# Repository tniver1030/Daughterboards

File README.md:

# Daughterboards
Various daughterboards and breakout not worth creating their own repo for

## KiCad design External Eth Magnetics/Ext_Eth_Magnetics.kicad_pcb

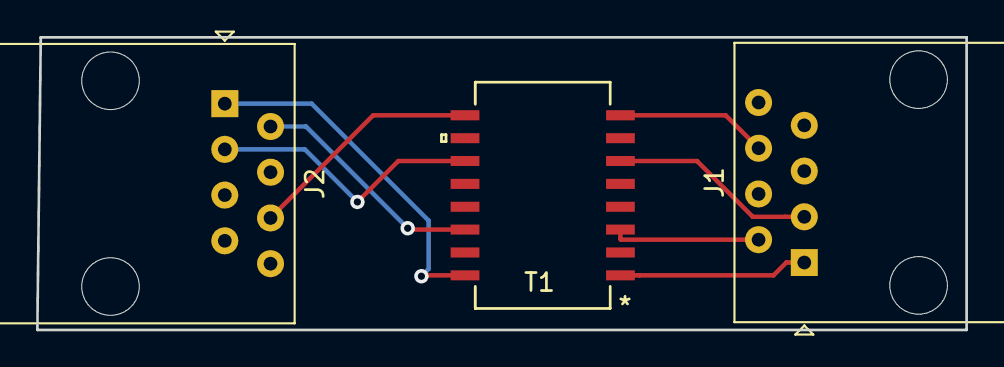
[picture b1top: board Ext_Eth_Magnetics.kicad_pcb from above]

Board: 2 copper layers, 51.6 x 16.3 mm, 3 parts (0 on the bottom side), 8 nets.

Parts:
J1, J2: RJ45; RJ45_Amphenol_54602-x08_Horizontal
T1: S558-5500-25-F

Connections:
unnamed: J1.1, T1.1
unnamed: J1.2, T1.3
unnamed: J1.3, T1.6
unnamed: J1.6, T1.8
unnamed: J2.1, T1.16
unnamed: J2.2, T1.14
unnamed: J2.3, T1.11
unnamed: J2.6, T1.9

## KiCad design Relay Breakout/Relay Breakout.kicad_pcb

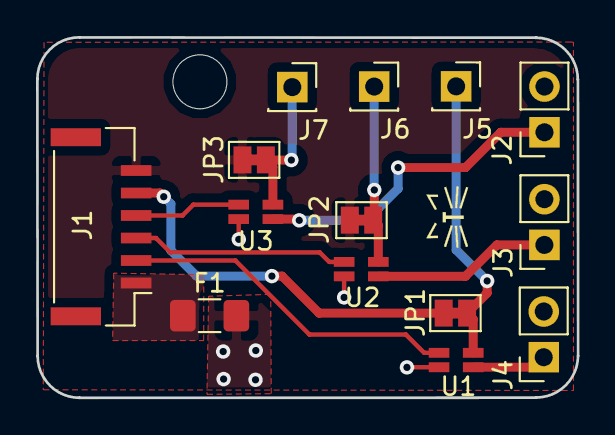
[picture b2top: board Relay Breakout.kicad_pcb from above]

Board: 2 copper layers, 30.0 x 20.0 mm, 14 parts (0 on the bottom side), 13 nets.

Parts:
F1: Fuse; Fuse_1206_3216Metric_Pad1.42x1.75mm_HandSolder
J1: Conn_01x06_Male; JST_GH_BM06B-GHS-TBT_1x06-1MP_P1.25mm_Vertical
J2, J3, J4: Conn_01x02_Female; PinSocket_1x02_P2.54mm_Vertical
J5, J6, J7: Conn_01x01_Female; PinSocket_1x01_P2.54mm_Vertical
JP1, JP2, JP3: SolderJumper_2_Bridged; SolderJumper-2_P1.3mm_Bridged_Pad1.0x1.5mm
U1, U2, U3: TLP3403R

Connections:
3V3DC: J1.5, JP1.2
5VDC: J1.6, JP2.2, JP3.2
GND: F1.2, J2.2, J3.2, J4.2, U1.2, U2.2, U3.2
GPIO1: J1.4, U3.1
GPIO2: J1.3, U2.1
GPIO3: J1.2, U1.1
unnamed: F1.1, J1.1
unnamed: J2.1, U3.3
unnamed: J3.1, U2.3
unnamed: J4.1, U1.3
unnamed: J5.1, JP1.1, U1.4
unnamed: J6.1, JP2.1, U2.4
unnamed: J7.1, JP3.1, U3.4

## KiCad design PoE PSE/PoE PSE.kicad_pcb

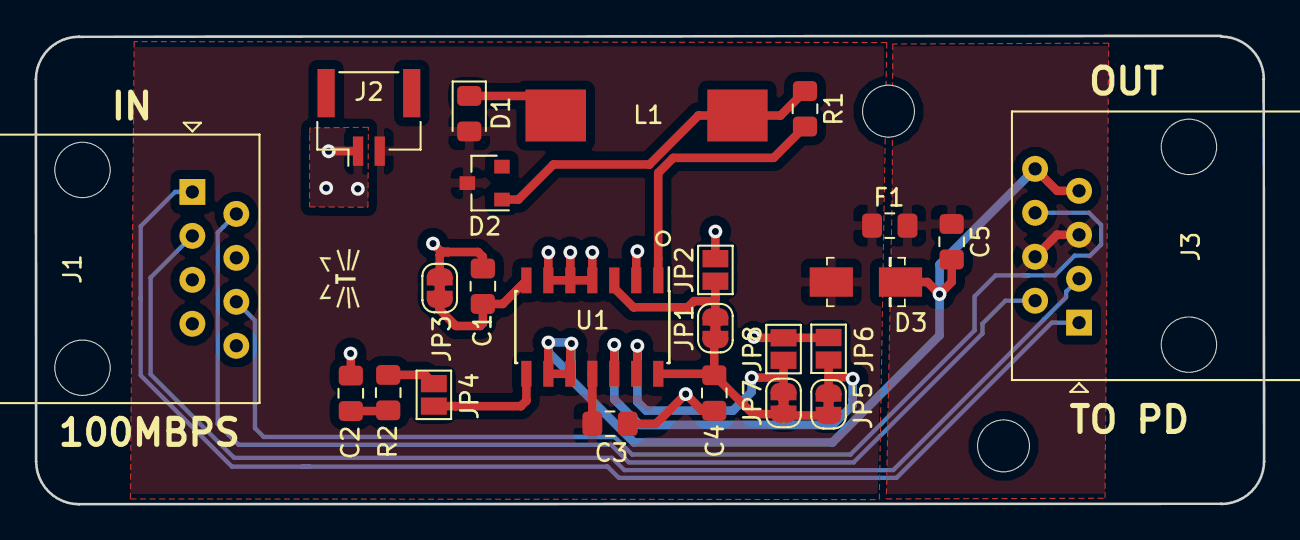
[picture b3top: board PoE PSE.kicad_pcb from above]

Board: 2 copper layers, 71.0 x 27.1 mm, 24 parts (0 on the bottom side), 19 nets.

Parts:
C1, C2, C4, C5: 0.1uF; C_0805_2012Metric_Pad1.15x1.40mm_HandSolder
C3: C; C_0805_2012Metric_Pad1.15x1.40mm_HandSolder
D1: LED; LED_0805_2012Metric_Pad1.15x1.40mm_HandSolder
D2: D; SOT-23
D3: D_TVS; DO-214AC
F1: Fuse; Fuse_0805_2012Metric_Pad1.15x1.40mm_HandSolder
J1, J3: RJ45; RJ45_Amphenol_54602-x08_Horizontal
J2: Conn_01x02; JST_GH_BM02B-GHS-TBT_1x02-1MP_P1.25mm_Vertical
JP1, JP3, JP5, JP7: SolderJumper_2_Bridged; SolderJumper-2_P1.3mm_Bridged_RoundedPad1.0x1.5mm
JP2, JP4, JP6, JP8: SolderJumper_2_Open; SolderJumper-2_P1.3mm_Open_Pad1.0x1.5mm
L1: INDUCTOR; SDR1005-103KL
R1, R2: R; R_0805_2012Metric_Pad1.15x1.40mm_HandSolder
U1: LTC4263; SOIC-14_3.9x8.7mm_P1.27mm

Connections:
ETH1: J1.1, J3.1
ETH2: J1.2, J3.2
ETH3: J1.3, J3.3
ETH6: J1.6, J3.6
unnamed: C1.1, JP3.1, U1.7
unnamed: C2.1, R2.2
unnamed: C5.1, F1.1, J3.4, J3.5
unnamed: C5.2, D3.1, J3.7, J3.8, U1.9, U1.10
unnamed: D1.1, L1.1
unnamed: D2.2, L1.2, R1.1
unnamed: JP1.2, JP2.1, U1.3
unnamed: JP4.1, U1.8
unnamed: JP4.2, R2.1
unnamed: JP5.2, JP6.1, U1.12
unnamed: JP7.2, JP8.1, U1.13
unnamed: R1.2, U1.1
VDD5: C4.1, JP1.1, JP5.1, JP7.1, U1.14
VDD48: C3.1, D1.2, D2.1, D3.2, F1.2, J2.2, U1.11
VSS: C1.2, C2.2, C3.2, C4.2, J2.1, JP2.2, JP3.2, JP6.2, JP8.2, U1.2, U1.4, U1.5, U1.6

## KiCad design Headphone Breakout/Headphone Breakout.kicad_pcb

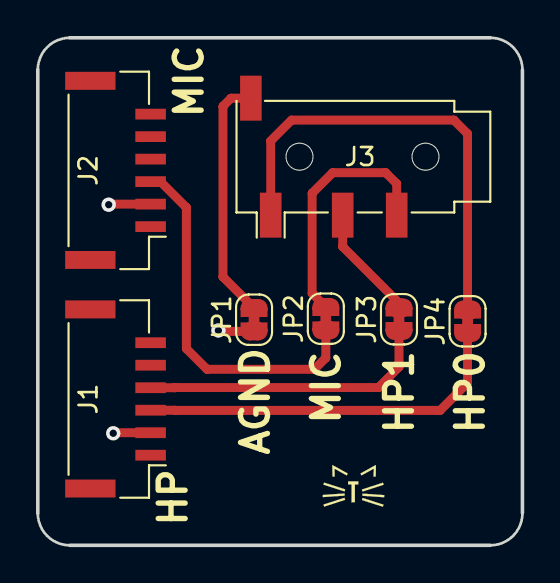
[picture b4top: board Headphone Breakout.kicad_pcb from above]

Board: 2 copper layers, 26.9 x 28.2 mm, 7 parts (0 on the bottom side), 11 nets.

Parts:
J1, J2: Conn_01x06_Male; JST_GH_BM06B-GHS-TBT_1x06-1MP_P1.25mm_Vertical
J3: AudioJack4_Ground; Jack_3.5mm_PJ320D_Horizontal
JP1, JP2, JP3, JP4: SolderJumper_2_Bridged; SolderJumper-2_P1.3mm_Bridged_RoundedPad1.0x1.5mm

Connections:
3V3: J1.5, J2.5
5V: J1.6, J2.6
AGND: J1.2, J2.2, JP1.1
DGND: J1.1, J2.1
HP0: J1.3, JP4.1
HP1: J1.4, JP3.1
MIC_0: J2.3, JP2.1
unnamed: J3.1, JP4.2
unnamed: J3.2, JP3.2
unnamed: J3.3, JP2.2
unnamed: J3.4, JP1.2

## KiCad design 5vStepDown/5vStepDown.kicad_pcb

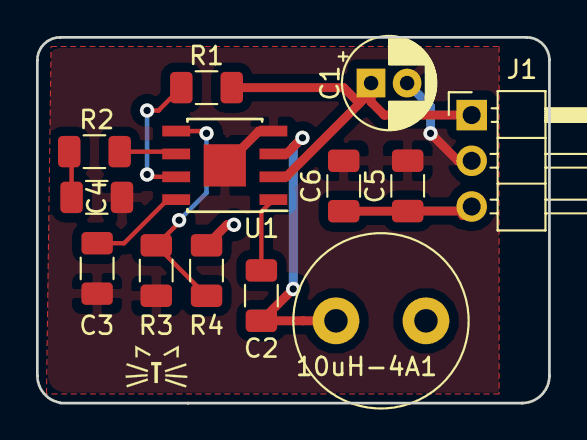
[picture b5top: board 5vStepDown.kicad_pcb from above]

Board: 2 copper layers, 28.4 x 20.3 mm, 13 parts (0 on the bottom side), 10 nets.

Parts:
10uH-4A1: INDUCTOR; L_Radial_D9.5mm_P5.00mm_Fastron_07HVP
C1: 10uF; CP_Radial_D5.0mm_P2.00mm
C2: 10nF; C_1206_3216Metric
C3: .1uF; C_1206_3216Metric
C4: 3.9nF; C_1206_3216Metric
C5, C6: 22uF; C_1206_3216Metric
J1: Conn_01x03_Male; PinHeader_1x03_P2.54mm_Horizontal
R1: R100K; R_1206_3216Metric
R2: 6.8k; R_1206_3216Metric
R3: 10k; R_1206_3216Metric
R4: 44.2k; R_1206_3216Metric
U1: MP2307; SOIC-8-1EP_3.9x4.9mm_P1.27mm_EP2.35x2.35mm

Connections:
GND: C1.2, C3.2, C5.2, C6.2, J1.2, R2.2, R3.2, U1.4, U1.9
INPUT: C1.1, J1.1, R1.2, U1.2
unnamed: 10uH-4A1.2, C2.2, U1.3
unnamed: C2.1, U1.1
unnamed: C3.1, U1.8
unnamed: C4.1, U1.6
unnamed: C4.2, R2.1
unnamed: R1.1, U1.7
unnamed: R3.1, R4.2, U1.5
OUTPUT: 10uH-4A1.1, C5.1, C6.1, J1.3, R4.1

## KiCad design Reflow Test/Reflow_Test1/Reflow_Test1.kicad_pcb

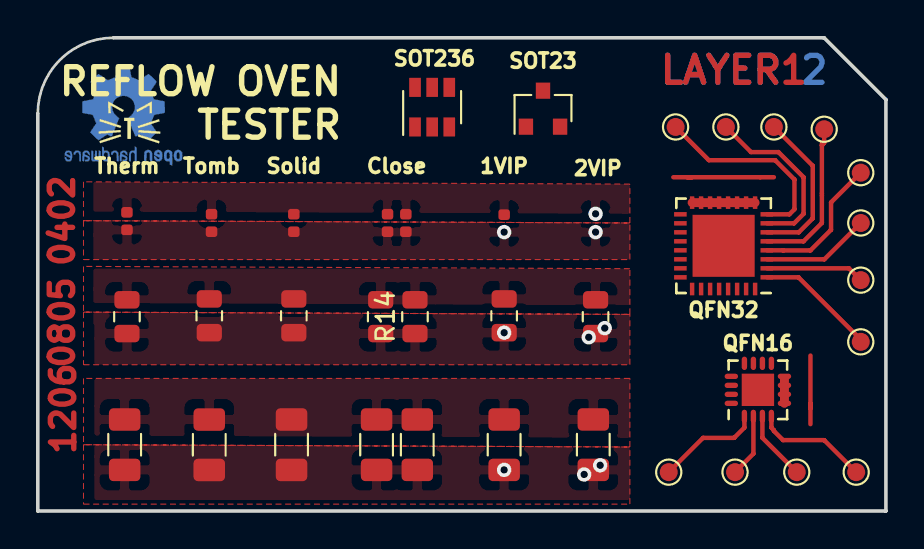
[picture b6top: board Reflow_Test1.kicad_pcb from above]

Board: 2 copper layers, 47.1 x 26.3 mm, 37 parts (0 on the bottom side), 16 nets.

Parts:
Q1: Q_NPN_BCE; SOT-23
R1, R4, R7, R10, R13, R16, R19: R; R_0402_1005Metric
R2, R5, R8, R11, R14, R17, R20: R; R_0805_2012Metric
R3, R6, R9, R12, R15, R18, R21: R; R_1206_3216Metric
TP1, TP2, TP3, TP4, TP5, TP6, TP7, TP8, TP9, TP10, TP11, TP12: TestPoint; TestPoint_Pad_D1.0mm
U1: PIC16F505-IMG; QFN-16-1EP_3x3mm_P0.5mm_EP1.8x1.8mm
U2: ATSAML21E15B-MUT; QFN-32-1EP_5x5mm_P0.5mm_EP3.45x3.45mm
U3: PAM8301; SOT-23-6

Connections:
GND: R1.2, R2.2, R3.2, R4.2, R5.2, R6.2, R7.2, R8.2, R9.2, R10.2, R11.2, R12.2, R13.2, R14.2, R15.2, R16.2, R17.2, R18.2, R19.2, R20.2, R21.2
unnamed: TP1.1, U2.4
unnamed: TP2.1, U2.5
unnamed: TP3.1, U2.3
unnamed: TP4.1, U1.4
unnamed: TP5.1, U2.6
unnamed: TP6.1, U2.2
unnamed: TP7.1, U2.7
unnamed: TP8.1, U2.1
unnamed: TP9.1, U2.8
unnamed: TP10.1, U1.1
unnamed: TP11.1, U1.2
unnamed: TP12.1, U1.3
unnamed: U1.5, U1.6, U1.7, U1.8
unnamed: U2.9, U2.10, U2.11, U2.12, U2.13, U2.14, U2.15, U2.16, U2.28
VCC: R1.1, R2.1, R3.1, R4.1, R5.1, R6.1, R7.1, R8.1, R9.1, R10.1, R11.1, R12.1, R13.1, R14.1, R15.1, R16.1, R17.1, R18.1, R19.1, R20.1, R21.1

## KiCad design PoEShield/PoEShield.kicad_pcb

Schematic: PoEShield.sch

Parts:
C1, C5: 0.1uF; C_0805_2012Metric_Pad1.15x1.40mm_HandSolder
C2: 22uF; C_1206_3216Metric_Pad1.42x1.75mm_HandSolder
C3: 1uF; C_1206_3216Metric_Pad1.42x1.75mm_HandSolder
C4: 10uF; C_1206_3216Metric_Pad1.42x1.75mm_HandSolder
C6, C7: 1nF 2kv; C_1206_3216Metric_Pad1.42x1.75mm_HandSolder
D1: SMAJ58JA; SMAJ58A-13-F
D2, D3: ABS2; Diode_Bridge_Diotec_ABS
F1: Fuse; Fuse_0805_2012Metric_Pad1.15x1.40mm_HandSolder
J1: RJ45; RJ45_Amphenol_54602-x08_Horizontal
J2: Conn_01x02_Male; JST_GH_BM02B-GHS-TBT_1x02-1MP_P1.25mm_Vertical
J3: Conn_01x03_Male; PinHeader_1x03_P2.54mm_Horizontal
L1: LQM2MPN4R7MG0L; L_0805_2012Metric_Pad1.15x1.40mm_HandSolder
R1: 287K; R_0805_2012Metric_Pad1.15x1.40mm_HandSolder
R2: 255; R_0805_2012Metric_Pad1.15x1.40mm_HandSolder
R3: 23.2k; R_0805_2012Metric_Pad1.15x1.40mm_HandSolder
R4: 1.62k; R_0805_2012Metric_Pad1.15x1.40mm_HandSolder
R5: 0; R_0805_2012Metric_Pad1.15x1.40mm_HandSolder
T1: S558-5500-25-F
U1: TPS2376-H; TI_SO-PowerPAD-8
U2: mEZS84801A
U3: PDQE10-Q48-S3-D; CONV_PDQE10-Q48-S3-D

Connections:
/3V3DC: J3.1, U2.17, U2.18
/12VDC: J3.3, U2.13, U2.14
/-VREG: C4.2, C7.2, U2.15, U2.16, U2.19, U2.20, U3.5
/VDD: C1.1, C2.1, D1.1, D2.1, D3.1, F1.2, J2.2, R3.1, U1.8
/VREG: C4.1, C6.2, J3.2, U3.3
/VSS: C1.2, D1.2, D2.2, D3.2, R1.2, R2.2, R4.2, U1.4, U1.9
unnamed: C2.2, C3.2, C5.2, C7.1, J2.1, U1.5, U3.1
unnamed: C3.1, C5.1, C6.1, L1.2, U3.2
unnamed: D2.3, T1.7
unnamed: D2.4, T1.2
unnamed: D3.3, J1.7, J1.8
unnamed: D3.4, J1.4, J1.5
unnamed: F1.1, L1.1
unnamed: J1.1, T1.1
unnamed: J1.2, T1.3
unnamed: J1.3, T1.6
unnamed: J1.6, T1.8
unnamed: R1.1, U1.1
unnamed: R2.1, U1.2
unnamed: R3.2, R4.1, U1.7
unnamed: R5.1, U1.6
unnamed: R5.2, U3.6
unnamed: T1.9, U2.10
unnamed: T1.11, U2.7
unnamed: T1.14, U2.6
unnamed: T1.16, U2.5

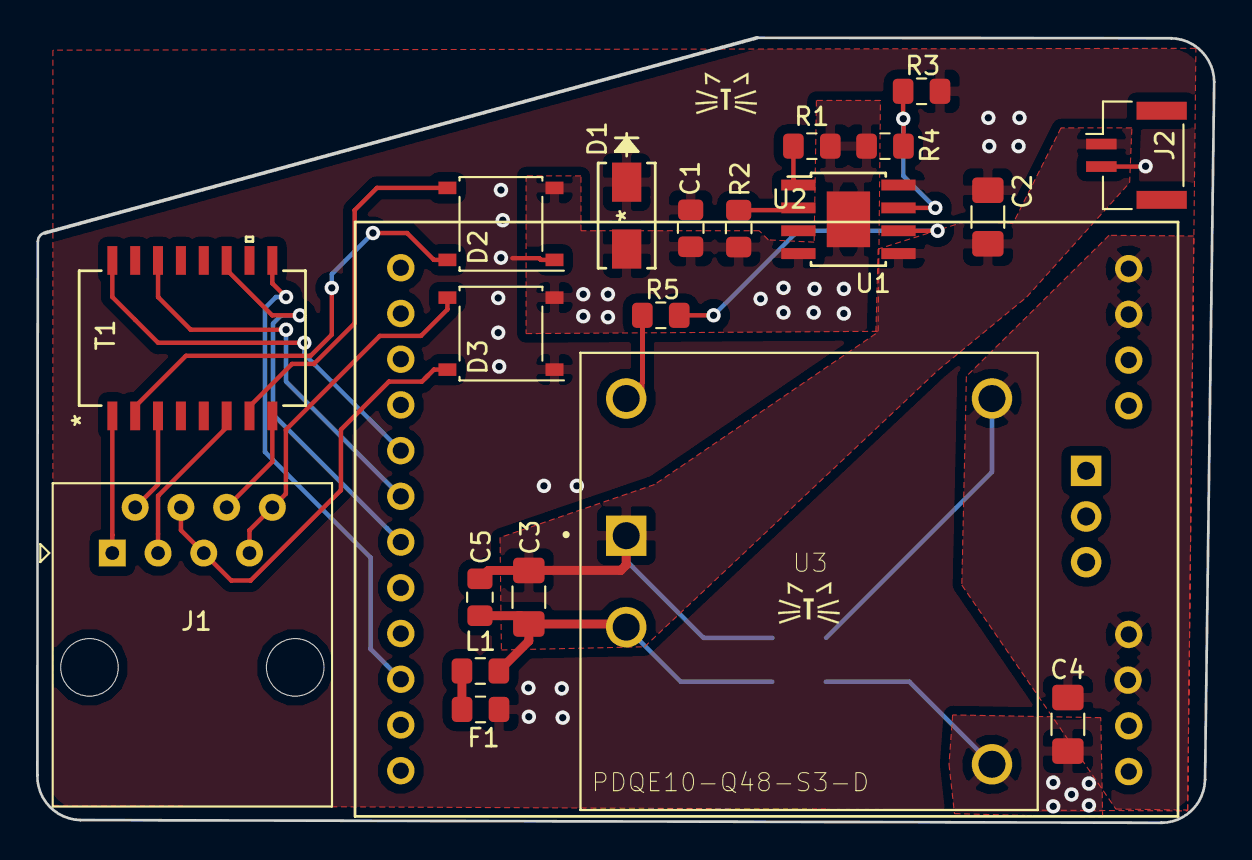
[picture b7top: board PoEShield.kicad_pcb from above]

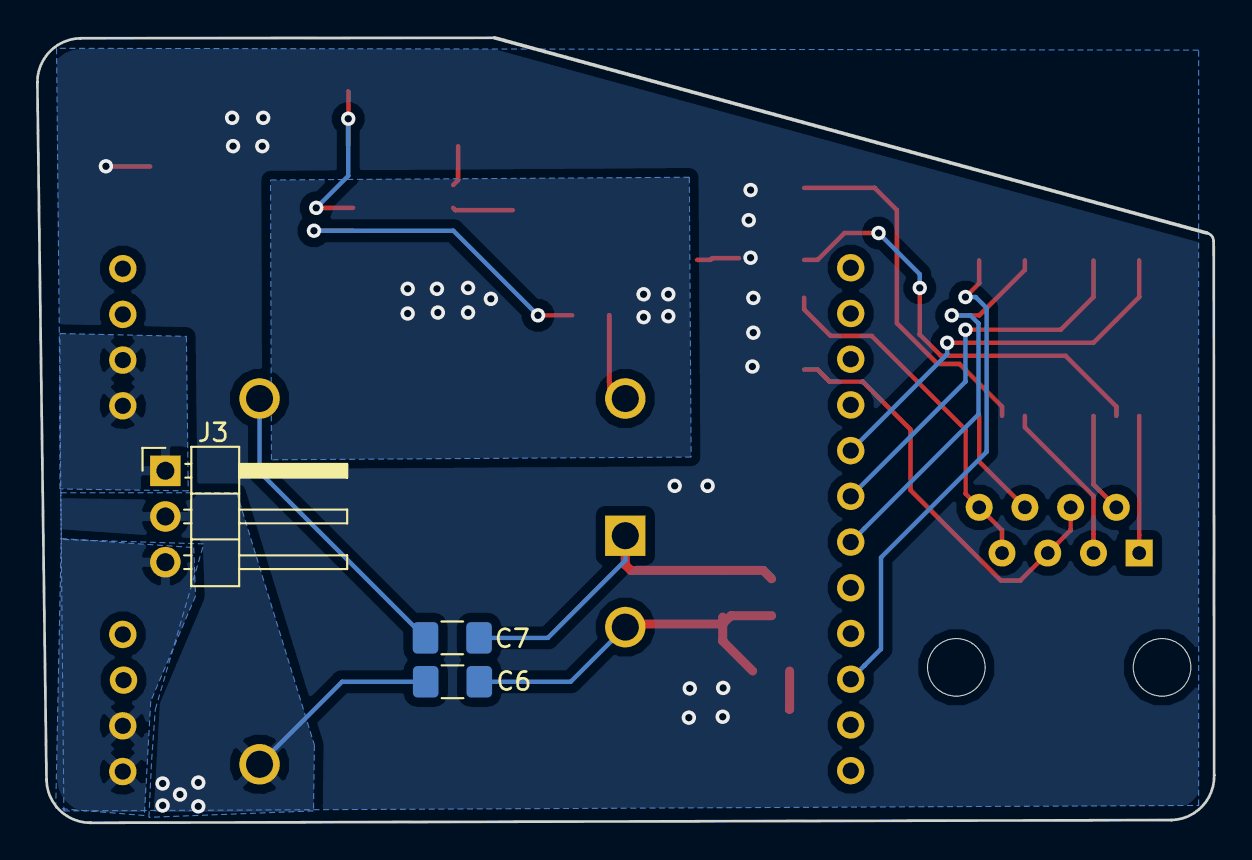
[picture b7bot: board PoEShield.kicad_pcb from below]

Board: 2 copper layers, 65.3 x 43.6 mm, 24 parts (3 on the bottom side), 26 nets.

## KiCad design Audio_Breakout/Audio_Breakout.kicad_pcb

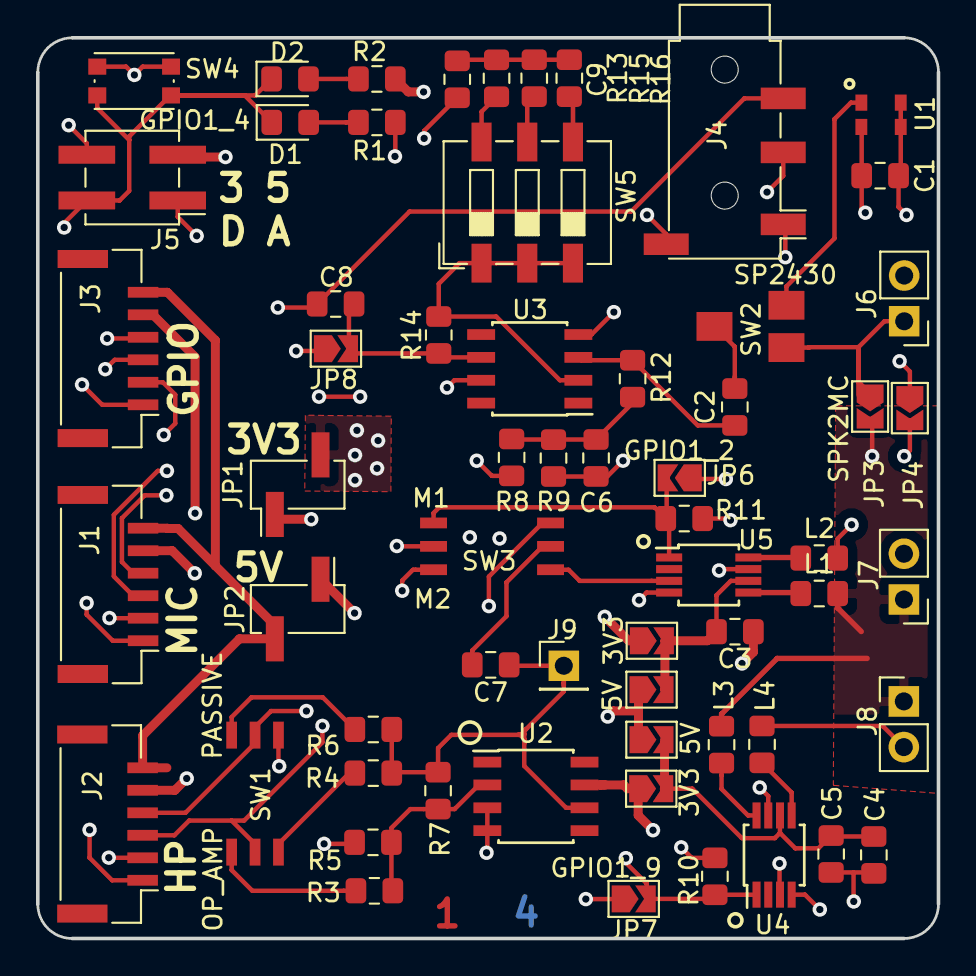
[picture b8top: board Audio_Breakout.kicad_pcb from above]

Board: 4 copper layers, 50.0 x 50.0 mm, 61 parts (0 on the bottom side), 45 nets.

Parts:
3V3, 3V3#2, 5V, 5V#2: SolderJumper_2_Open; SolderJumper-2_P1.3mm_Open_TrianglePad1.0x1.5mm
C1, C5: 0.1uF; C_0805_2012Metric_Pad1.15x1.40mm_HandSolder
C2, C3, C9: 1uF; C_0805_2012Metric_Pad1.15x1.40mm_HandSolder
C4: 10uF; C_0805_2012Metric_Pad1.15x1.40mm_HandSolder
C6: 2uF; C_0805_2012Metric_Pad1.15x1.40mm_HandSolder
C7: 47nF; C_0805_2012Metric_Pad1.15x1.40mm_HandSolder
C8: C; C_0805_2012Metric_Pad1.15x1.40mm_HandSolder
D1, D2: LED; LED_0805_2012Metric_Pad1.15x1.40mm_HandSolder
J1, J2, J3: Conn_01x06_Male; JST_GH_BM06B-GHS-TBT_1x06-1MP_P1.25mm_Vertical
J4: AudioJack4_Ground; Jack_3.5mm_PJ320D_Horizontal
J5: Conn_01x04_Female; PinHeader_2x02_P2.54mm_Vertical_SMD
J6, J7, J8: Conn_01x02_Female; PinHeader_1x02_P2.54mm_Vertical
J9: Conn_01x01_Female; PinHeader_1x01_P2.54mm_Vertical
JP1, JP2: Jumper; PinHeader_1x02_P2.54mm_Vertical_SMD_Pin1Left
JP3, JP4, JP6, JP7, JP8: SolderJumper_2_Open; SolderJumper-2_P1.3mm_Open_TrianglePad1.0x1.5mm
L1, L2, L3, L4: Ferrite_Bead_Small; R_0805_2012Metric_Pad1.15x1.40mm_HandSolder
R1, R2, R4, R6, R10, R11: R; R_0805_2012Metric_Pad1.15x1.40mm_HandSolder
R3, R5: 10k; R_0805_2012Metric_Pad1.15x1.40mm_HandSolder
R7: 100; R_0805_2012Metric_Pad1.15x1.40mm_HandSolder
R8, R9: 47k; R_0805_2012Metric_Pad1.15x1.40mm_HandSolder
R12, R14: 100k; R_0805_2012Metric_Pad1.15x1.40mm_HandSolder
R13, R15, R16: 11k; R_0805_2012Metric_Pad1.15x1.40mm_HandSolder
SW1, SW3: CS-4-22YTB; CS-4-22YB
SW2: CS-4-12XTA; CS-4-12XA
SW4: SW_Push; SW_SPST_KMR2
SW5: SW_DIP_x03; SW_DIP_SPSTx03_Slide_6.7x9.18mm_W6.73mm_P2.54mm_LowProfile_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
U1: spw2430; SPW2430
U2, U3: OPA1641; SOIC-8_3.9x4.9mm_P1.27mm
U4: SSM2305; MSOP-8_3x3mm_P0.65mm
U5: PAM8302AAS; MSOP-8_3x3mm_P0.65mm

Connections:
3V3DC: 3V3.1, 3V3#2.1, C1.1, J5.4, JP1.2, R1.1, R8.1, SW3.5, U1.4, U2.7, U3.7
5VDC: 5V.1, 5V#2.1, J5.3, JP2.1, R2.1
AGND: C1.2, C3.1, C4.1, C5.1, C6.2, C9.2, J1.2, J2.2, J4.4, J5.1, J6.2, JP4.1, R9.2, R10.2, R11.1, U1.2, U1.3, U2.3, U2.4, U3.4, U4.4, U4.7, U5.4, U5.7
AUD_OUT+: J7.1, J8.1, JP3.2, L1.2, L3.2
AUD_OUT-: J7.2, J8.2, JP4.2, L2.2, L4.2
DGND: D1.1, D2.1, J1.1, J2.1, J3.1, J5.2, SW4.2
GPIO1_2: J3.2, JP6.1
GPIO1_4: J3.4, SW4.1
GPIO1_9: J3.3, JP7.1
HP_0: J2.3, J4.1, SW1.5
HP_1: J2.4, J4.2, SW1.2
MIC_0: C8.1, J1.3, J4.3
MIC_1: J1.4, JP8.1
Mono1: SW3.1, U5.3
Mono2: SW3.3, U4.3
unnamed: C2.1, R12.2, U3.3
unnamed: C2.2, SW2.1
unnamed: 3V3#2.2, 5V#2.2, C3.2, U5.6
unnamed: 3V3.2, 5V.2, C4.2, C5.2, U4.6
unnamed: C6.1, R8.2, R9.1, R12.1
unnamed: C7.1, SW3.2
unnamed: C7.2, J9.1, R4.1, R6.2, R7.2, U2.6
unnamed: C8.2, JP8.2, R14.1, U3.6
unnamed: C9.1, R13.2, R15.2, R16.2
unnamed: D1.2, R1.2
unnamed: D2.2, R2.2
unnamed: J1.5, J2.5, J3.5, JP1.1
unnamed: J1.6, J2.6, J3.6, JP2.2
unnamed: J6.1, JP3.1, SW2.2
unnamed: L1.1, U5.5
unnamed: L2.1, U5.8
unnamed: L3.1, U4.8
unnamed: L4.1, U4.5
unnamed: R3.1, SW1.4
unnamed: R3.2, R5.2, R7.1, U2.2
unnamed: R4.2, SW1.6
unnamed: R5.1, SW1.1
unnamed: R6.1, SW1.3
unnamed: R13.1, SW5.6
unnamed: R14.2, SW5.1, SW5.2, SW5.3, U3.2
unnamed: R15.1, SW5.5
unnamed: R16.1, SW5.4
unnamed: SW2.3, U1.1
ON_MONO1: JP6.2, R11.2, SW3.4, U5.1
ON_MONO2: JP7.2, R10.1, SW3.6, U4.1

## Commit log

2019-05-07 Init Commit
2019-05-14 Created Readme
2019-05-23 Created Ethernet Magnetics Midspan
2019-07-01 Updated resistor values
2019-09-12 Made header crossover jumper. Started audio breakout to support two-way comm from speaker

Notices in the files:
parts and their libraries:
Copyright 2016 Accelerated Designs. All rights reserved.
